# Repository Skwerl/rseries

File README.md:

FioSaber R-Series Control
=======

Arduino Controller &amp; Receiver for R2-D2

Note that there are multiple branches for this repository. I'm currently working on an experimental new controller based on a custom shield I designed for the Arduino Fio. See the **traditional** branch for code for the "standard" R-Series controller/receiver hardware by Michael Erwin & Co. My current work (master branch) uses a custom controller with the Erwin receiver.

***

Controller Hardware Details: Coming Soon! Custom shield for Arduino Fio v3, in prototype phase.  
Receiver Hardware Details: https://code.google.com/p/rseries-open-control/

***

Controller requires patch to XBee library. As documented [here](http://forum.arduino.cc/index.php?topic=111354.0 "Serial compile issue"), in XBee.cpp, the following code:

`_serial = &Serial;`

Needs to be replaced with:

```
#if defined(USBCON)
  _serial = &Serial1;
#else
  _serial = &Serial;
#endif
```

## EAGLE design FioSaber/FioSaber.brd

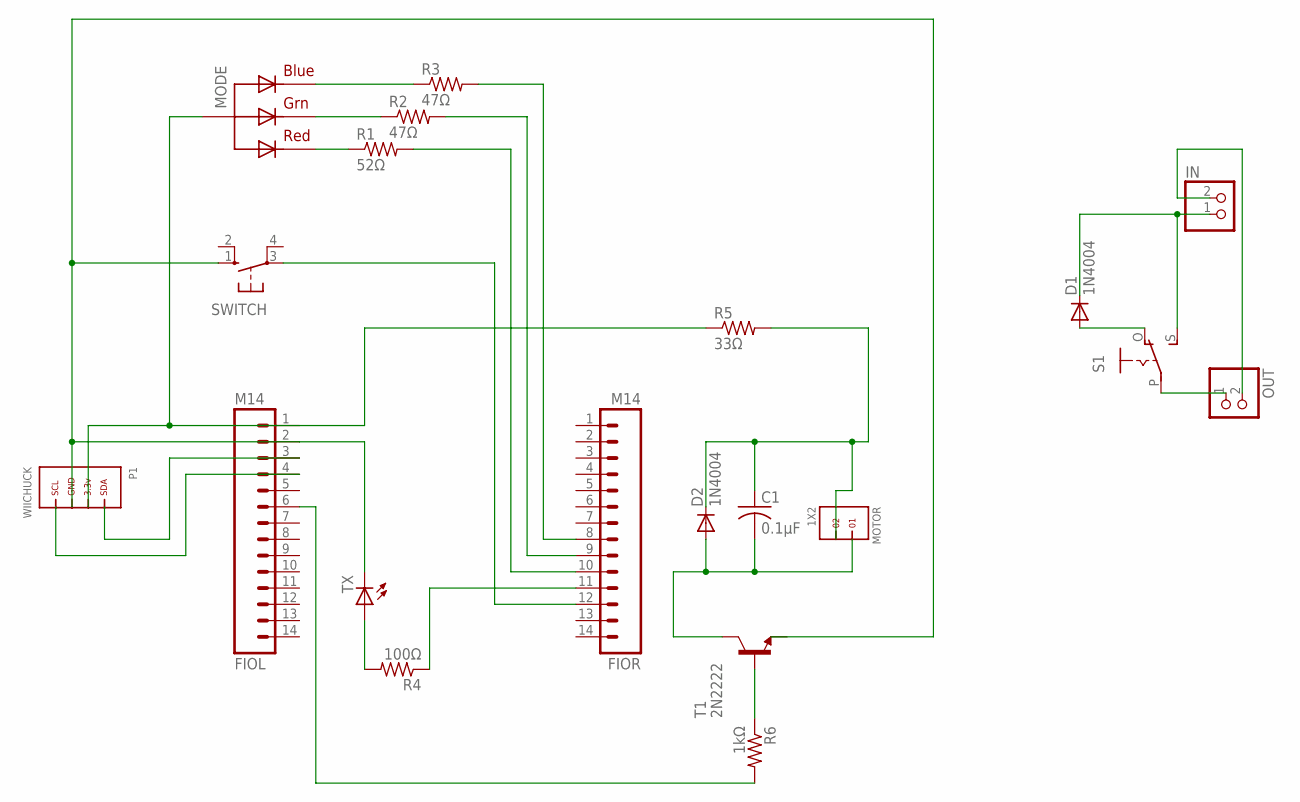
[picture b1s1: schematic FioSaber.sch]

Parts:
C1: 0.1µF; C025-025X050
D1, D2: 1N4004; DO41-10
FIOL: M14; 1X14
FIOR: M14; 1X14
IN: JST_2PIN-THM-RA; JST-PH-2-THM-RA
MODE: RGBLED_CA-PIRANHA; PIRANHA5MM
MOTOR: 1X2
OUT: JST_2PIN-THM-RA; JST-PH-2-THM-RA
P1: WIICHUCK; MEMOREX_RECEIVER
R1: 52Ω; 0207/7
R2, R3: 47Ω; 0207/7
R4: 100Ω; 0207/7
R5: 33Ω; 0207/7
R6: 1kΩ; 0207/7
S1: EG1218S; EG1218
SWITCH: 10-XX; B3F-10XX
T1: 2N2222; TO92-EBC-OVAL
TX: LED3MM

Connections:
unnamed: FIOL.1, MODE.4 (VCC), P1.SDA, R5.1
unnamed: D1.C, IN.1 (2), S1.S
unnamed: FIOL.4, P1.GND
unnamed: FIOL.3, P1.PWR
unnamed: D1.A, S1.O
unnamed: MODE.2 (RED), R1.1
unnamed: MODE.3 (GREEN), R2.1
unnamed: MODE.1 (BLUE), R3.1
unnamed: OUT.1 (2), S1.P
unnamed: IN.2 (1), OUT.2 (1)
unnamed: FIOR.12, SWITCH.3
unnamed: FIOR.10, R1.2
unnamed: FIOR.9, R2.2
unnamed: FIOR.8, R3.2
unnamed: FIOL.6, R6.2
unnamed: FIOR.11, R4.1
unnamed: R6.1, T1.B
unnamed: C1.2, D2.A, MOTOR.1, T1.C
unnamed: C1.1, D2.C, MOTOR.2, R5.2
unnamed: FIOL.2, P1.SCL, SWITCH.1 (S), TX.K (C)
unnamed: R4.2, TX.A

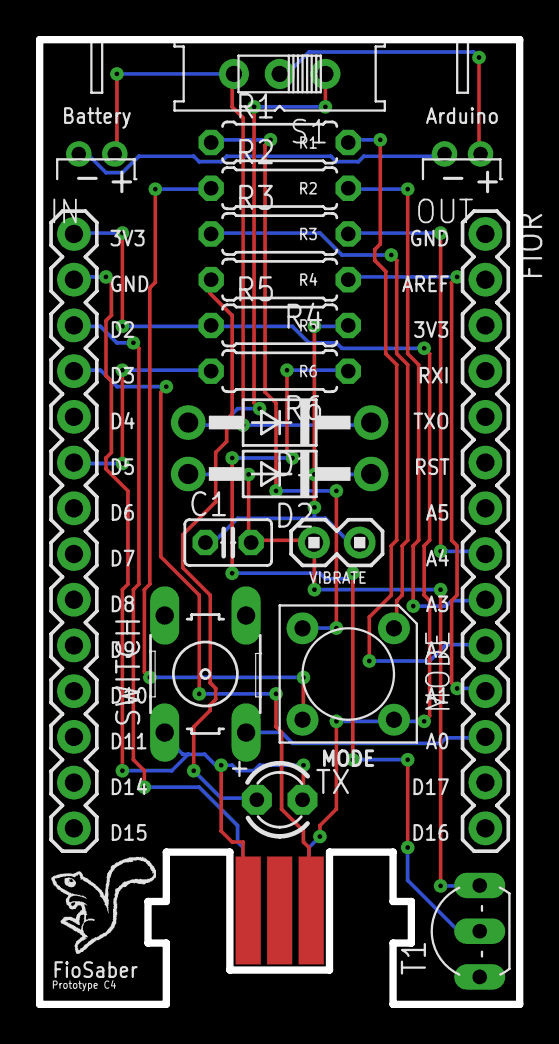
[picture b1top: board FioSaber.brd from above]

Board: 2 copper layers, 26.7 x 53.6 mm, 20 parts (0 on the bottom side), 21 nets.

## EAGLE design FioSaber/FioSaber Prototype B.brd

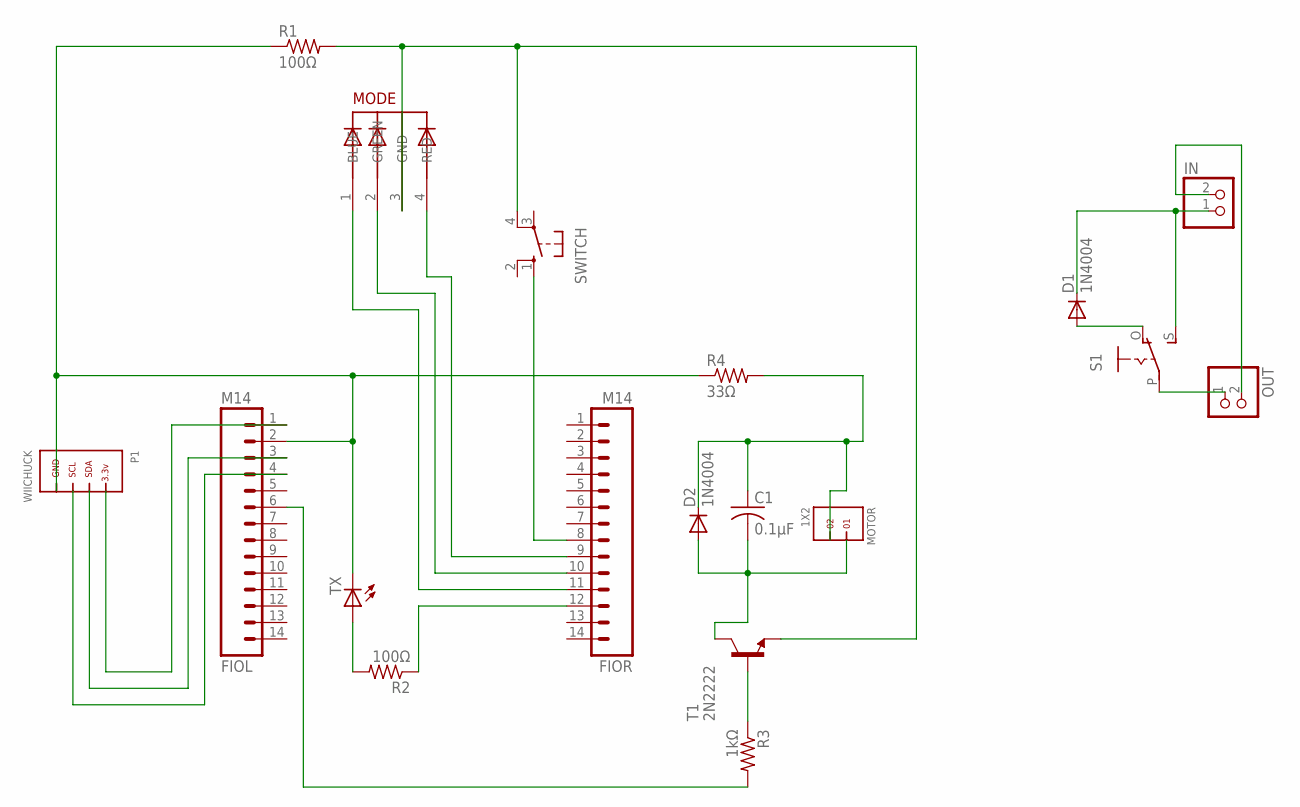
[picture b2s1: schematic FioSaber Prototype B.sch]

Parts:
C1: 0.1µF; C025-025X050
D1, D2: 1N4004; DO41-10
FIOL: M14; 1X14
FIOR: M14; 1X14
IN: JST_2PIN-SMT-RA; JST-PH-2-SMT-RA
MODE: 5MMRGBLED; LED5MMRGB
MOTOR: 1X2
OUT: JST_2PIN-SMT-RA; JST-PH-2-SMT-RA
P1: WIICHUCK; MEMOREX_RECEIVER
R1, R2: 100Ω; 0207/7
R3: 1kΩ; 0207/7
R4: 33Ω; 0207/7
S1: EG1218S; EG1218
SWITCH: 10-XX; B3F-10XX
T1: 2N2222; TO92-EBC-OVAL
TX: LED3MM

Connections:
unnamed: FIOL.1, P1.PWR
unnamed: D1.C, IN.1 (2), S1.S
unnamed: FIOL.3, P1.SDA
unnamed: FIOL.4, P1.SCL
unnamed: D1.A, S1.O
unnamed: FIOR.11, MODE.1 (BLUE)
unnamed: FIOR.10, MODE.2 (GREEN)
unnamed: FIOR.9, MODE.4 (RED)
unnamed: FIOL.2, P1.GND, R1.1, R4.1, TX.K (C)
unnamed: OUT.1 (2), S1.P
unnamed: IN.2 (1), OUT.2 (1)
unnamed: MODE.3 (GND), R1.2, SWITCH.4 (P1), T1.E
unnamed: FIOR.8, SWITCH.1 (S)
unnamed: FIOL.6, R3.2
unnamed: FIOR.12, R2.1
unnamed: R3.1, T1.B
unnamed: C1.2, D2.A, MOTOR.1, T1.C
unnamed: C1.1, D2.C, MOTOR.2, R4.2
unnamed: R2.2, TX.A

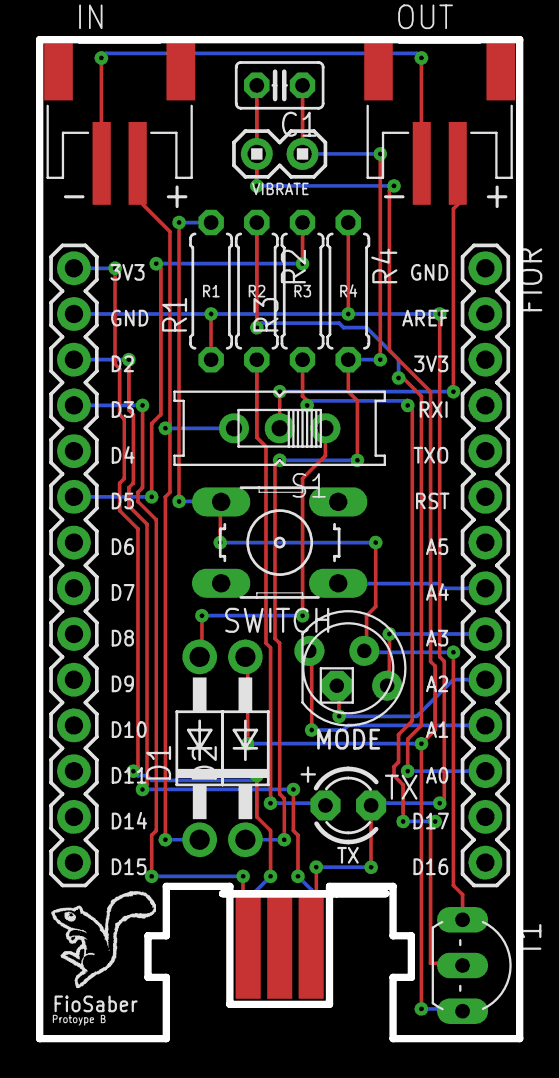
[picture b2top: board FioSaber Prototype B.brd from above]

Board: 2 copper layers, 26.7 x 55.5 mm, 18 parts (0 on the bottom side), 19 nets.

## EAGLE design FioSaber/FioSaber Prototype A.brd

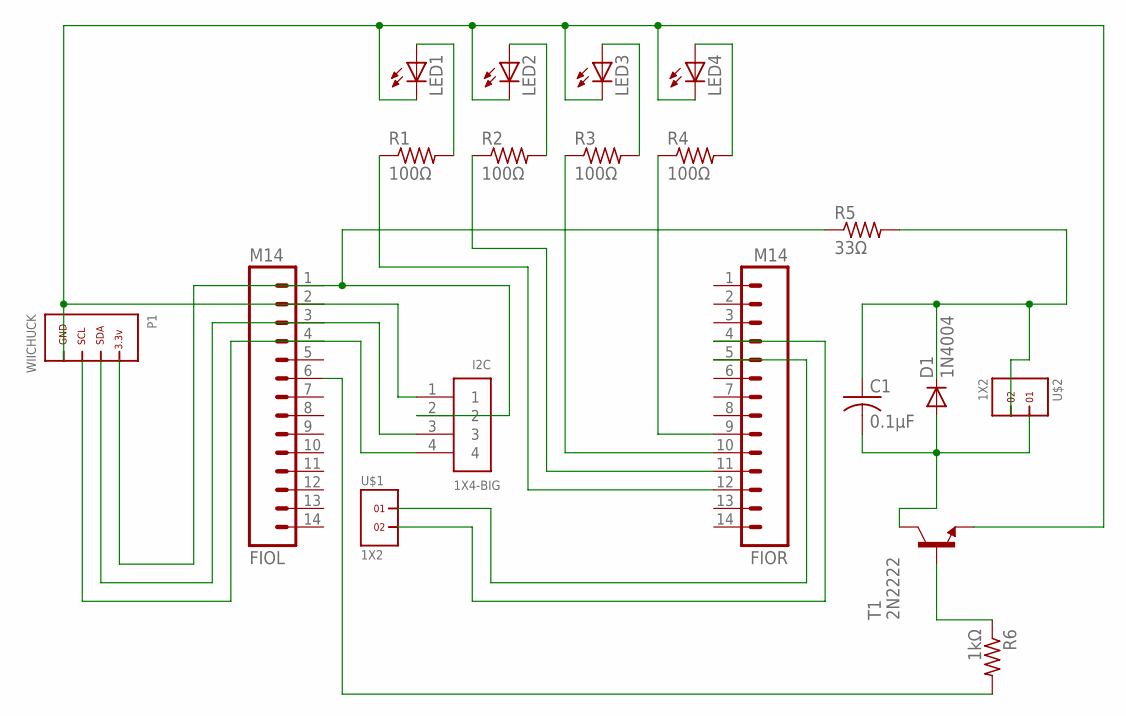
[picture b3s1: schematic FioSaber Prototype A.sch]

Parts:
C1: 0.1µF; C025-025X050
D1: 1N4004; DO41-10
FIOL: M14; 1X14
FIOR: M14; 1X14
I2C: 1X4-BIG; 1X04-BIG
LED1, LED2, LED3, LED4: LED3MM
P1: WIICHUCK; MEMOREX_RECEIVER
R1, R2, R3, R4: 100Ω; 0207/10
R5: 33Ω; 0207/10
R6: 1kΩ; 0207/10
T1: 2N2222; TO92-EBC-OVAL
U$1, U$2: 1X2

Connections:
unnamed: FIOL.1, I2C.2, P1.PWR, R5.1
unnamed: FIOL.3, I2C.3, P1.SDA
unnamed: FIOL.4, I2C.4, P1.SCL
unnamed: FIOR.12, R1.1
unnamed: FIOR.11, R2.1
unnamed: FIOR.10, R3.1
unnamed: FIOR.9, R4.1
unnamed: LED1.A, R1.2
unnamed: LED2.A, R2.2
unnamed: LED3.A, R3.2
unnamed: LED4.A, R4.2
unnamed: FIOL.2, I2C.1, LED1.K (C), LED2.K (C), LED3.K (C), LED4.K (C), P1.GND, T1.E
unnamed: FIOR.4, U$1.2
unnamed: FIOR.5, U$1.1
unnamed: FIOL.6, R6.2
unnamed: R6.1, T1.B
unnamed: C1.2, D1.A, T1.C, U$2.1
unnamed: C1.1, D1.C, R5.2, U$2.2

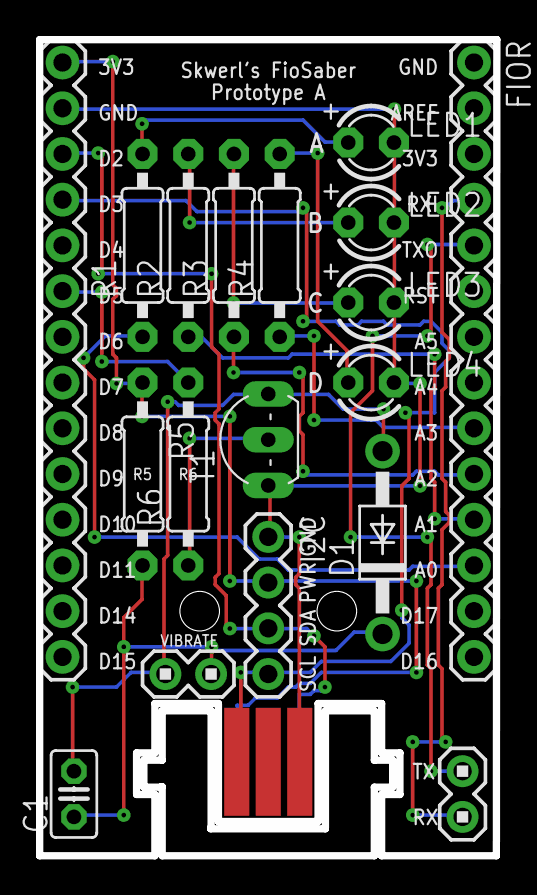
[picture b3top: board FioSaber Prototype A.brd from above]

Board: 2 copper layers, 25.4 x 45.3 mm, 19 parts (0 on the bottom side), 18 nets.

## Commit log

2013-09-02 network check isn't verifying the specific pan id yet, just that there is one
2013-09-14 SNOOPY DANCE
2013-09-14 Trying to get the MP3Trigger responding...
2013-09-14 Ditched MP3Trigger.h library… We have sound!
2013-09-14 Adding sound library to Github
2013-09-14 Random sounds by user-controlled "mood" trigger!
2013-09-15 down+c stops sound
2013-09-15 controller verifies connection with receiver
2013-09-15 cleaning / reorganization
2013-09-15 messing with menu screens
2013-09-15 cleaning & reorg
2013-09-15 beginning grid display
2013-09-16 evolving the trigger grid...
2013-09-16 touchscreen pagination working!
2013-09-16 wayyy better way of knowing what trigger was pressed
2013-09-16 working touch screen triggers!
2013-09-16 nitpicking
2013-09-18 added laugh button, fixed trigger ids
2013-09-23 working on the rssi, battery level & status bar
2013-09-23 better (and dual) battery display
2013-09-23 sticky buttons
2013-09-24 working sticky triggers
2013-09-24 cleanup
2013-09-24 updated boot, tx signal
2013-09-27 controller code cleanup
2013-09-27 starting receiver servo setup
2013-09-27 dome motor control over pwm channel
2013-09-27 configure pins for up to 10 servo channels
2013-09-27 holo activation
2013-09-27 holo trigger on controller
2013-09-27 nitpicking voltage display
2013-09-27 woring rssi, simpler telemetry
2013-09-27 5 bars for rssi
2013-09-27 nitpicks
2013-09-27 not sure why this fixes receiver...
2013-09-28 tweaks to battery display
2013-09-28 tweaks to dome rotation logic
2013-09-29 sticky moods, better sticky buttons
2013-09-29 autopilot mode, better dome spinning
2013-09-29 autopilot tweaks
2013-09-29 undoing the sticky button fix
    this makes every signal lag. what i really need to do is confirm each
    trigger signal was received, once and only once.
2013-09-30 two-way com between controller/receiver
    controller now shows whether or not a signal was executed by receiver,
    or if the receiver has stopped responding.
2013-09-30 better touch screen buttons
    no accidental double-clicks, and sticky buttons only flip if receiver
    has verified the toggle.
2013-10-03 autopilot tweak
2013-10-04 let's not send so many packets
    reworked timing of telemetry collection and transmission
2013-10-04 autopilot tweaks
    still seeing an odd issue where sometimes autopilot just plays constant
    sounds with no dome rotation
2013-10-04 autopilot tweaks
    not sure why this fixes autopilot issue
2013-10-05 nunchuk pairing/unlock
    thanks micke!
2013-10-13 new screen had a weird quirk
2013-10-13 controller tweaks
2013-12-05 adding custom fio shield pcb designs
2013-12-05 vibraton motor
2013-12-05 added fiosaber gerbers
2013-12-05 gerbers ready for fab
2013-12-05 gerbers for fab
2013-12-05 schematic tweaks
2013-12-09 prototype b
2013-12-09 renamed protoype a
2013-12-12 added manual mode switch
2013-12-12 re-marking two pins
2013-12-20 labeled motor header
2013-12-22 documented xbee.cpp patch
2013-12-22 FioSaber Protoype A initial build
2013-12-22 clarity on new branch
2013-12-22 title on readme.md
2013-12-22 title on fiosaber control readme
2013-12-22 playing with xbee rate
2013-12-22 removing fiosaber stuff from traditional branch
2013-12-22 proper mode switching, stripped out all of the old r-series stuff
2013-12-22 mode switching cleanup
2013-12-22 figured out why the vibe doesn't work
2013-12-22 fixed vibe motor circuit
2013-12-22 reconfigured prototype b
2013-12-23 prototype b tweaks
2013-12-24 prototype b gerbers
2013-12-24 tweaked prototype b gerbers
2013-12-24 tweaks to prototype b gerbers
2013-12-24 pin label tweaks
2013-12-25 very preliminary release candidate
2013-12-28 board tweaks
2013-12-29 back to square board
2013-12-29 planning on supporting wii classic controller for unstealth option
2013-12-29 adding libraries
2014-01-19 prototype c off to fab
2014-02-01 implemented pirhana rgb led
2014-02-01 fixed switch issue
2014-02-23 prototype c switch works correctly now
2014-08-15 dome speed adjustment for pittman
2014-08-16 2-axis front holo movement
2014-08-16 removed stray debug
2014-08-22 killed autopilot, programmed drive mode
2014-08-30 way better differential drive!
2014-08-31 safety brake
2014-08-31 cleanup new differential drive code
2014-11-29 fixed haptic circuit, prototype c3 for fab
2015-10-04 Added vibe motor code, fixed txLED
2015-10-04 FioSaber Prototype C4
2022-09-16 And we're back
2022-09-16 Not compiling without this change
2023-04-30 Updated libs
2023-04-30 Updated code for new libs & IDE, killed the jitters!
